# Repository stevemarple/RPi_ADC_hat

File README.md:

# Raspberry Pi ADC hat

A Raspberry Pi hat using the Microchip MCP3424 analogue to digital
converter. The hat also has connectors for I2C and 1-wire interfaces,
and two switched outputs, for instance to control fans, motors or
relays. A Honeywell HIH6130-021 or HIH6131-021 I2C temperature and
humidity sensor can also be fitted.

## Hardware features

### Analogue to digital converter

The MCP3424 is a 4 channel 18 bit differential input analogue to
digital converter. Sample rates are 3.75 SPS (samples per second) at
18 bit resolution, 15 SPS at 16 bit resolution, 60 SPS at 14 bit
resolution and 240 SPS at 12 bit resolution. When single-ended inputs
are used the resolution is reduced by 1 bit. A jumper block enables
the I2C address of the MCP3424 to be selected from eight possible
values. The ADC inputs are directly wired to a 9 pin D connector, 3
channels can be used for differential inputs, the fourth for
single-ended measurements only. Optional decoupling capacitors can be
added to all inputs; alternatively zero ohm resistors may be used to
convert the differential inputs to single-ended.

### I2C interface

The buffered I2C interface is made available via an RJ11 connector,
allowing additional MCP3424 devices or other I2C devices to be
connected, eg the AuroraWatchNet magnetometer sensor head
(https://github.com/stevemarple/AuroraWatchNet/tree/master/hardware/FLC100_shield/remote_v2). 

### 1-wire interface

A connector for a 1-wire interface is provided. The 3 pin Molex
connector also connects to the Raspberry Pi's 3.3V supply so that it
is not necessary to use parasitic power operation.

### Power supplies

All power is used is taken from the Raspberry Pi via the GPIO
header. The 1 wire interface, I2C buffer and HAT EEPROM are connected
to the Pi's 3.3V supply, all other power is derived from the 5V
supply. Changes in the CPU load on the Pi can result in small supply
voltage variations due to voltage sag from the Pi's power supply. When
sensors and the ADC are powered directly from the Pi's 5V supply this
can result in spurious measurements. To combat this effect a DC-DC
converter and linear regulator can be fitted to derive a stable
analogue voltage supply.

### Switched outputs

Two switched outputs are provided which can be connected to fans,
motors, relays etc. Flyback diodes can be fitted to allow safe switching
of inductive loads.

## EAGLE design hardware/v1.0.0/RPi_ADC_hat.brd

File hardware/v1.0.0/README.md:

# Build instructions for v1.0.0

The PCB design offers a number of options for construction, not all
parts should fitted. Indeed, to do so could be harmful to the ADC
HAT and to the Raspberry Pi. Read and understand the build options first.

## Build options

### Linear voltage regulator

Decide upon the analogue supply voltage for your application. The
analogue voltage sets the operating voltage for MCP3424 ADC, and the
signal levels for the buffered section of the I2C bus. There are four
options:

1. For 3.3V operation fit a Microchip TC1262-33VDB. Do not fit the
DC-DC converter, instead fit the DC-DC converter link wire.
2. For a clean 5V analogue supply fit a Microchip MCP1790-5002E/DB
voltage regulator and a DC-DC converter.
3. To reuse the Raspberry Pi's 5V supply (not recommended) do not fit
a voltage regulator and do not fit the DC-DC converter. Fit the link
wires for both the DC-DC converter and the voltage regulator.
4. To delegate the analogue voltage supply generation to an external
board connected via the I2C interface connector X1 do not fit the
voltage regulator or the voltage regulator link wire. Whether the
DC-DC converter should also be fitted depends on the input voltage
required for the external regulator; it can be powered from either the
Pi's 5V supply or the DC-DC converter's output, selected by the
position of the jumper on JP1.

Under no circumstances should the linear regulator and its link wire
be fitted.

Fit JP1 only if option 4 is selected.

### DC-DC converter

The standard DC-DC converter is the  Traco TME0509S. Alternatives
include the Murata NME0509SC and the Recom Power RO-0509S. All
convert 5V DC to 9V DC. Provided the recommended voltage ratings for
the capacitors are followed it is also possible to use 5V to 12V DC-DC
converters.

The reference build is to include a DC-DC converter. If one is not
required then a link wire can be fitted in its place. Under no
circumstances should a DC-DC converter be fitted and its link wire.

It is also possible to use an external supply instead of the DC-DC
converter by fitting a Molex 22-23-2041 connector in its place.

If it is found that the load on the DC-DC converter is insufficient
for correct operation it is possible to fit an optional load resistor
(R3). Do not exceed power rating for the resistor; a 1210
surface-mount resistor can be fitted which is likely to have a higher
rating than the 1206 package.

### ADC

If the onboard ADC is not required (for instance, using external
devices connected to the I2C interface) then omit U4, U6, C6, C11, C12,
C13, C14, C15, C16, C17, X2 and JP2. The reference build is to fit U4,
C6, X2 and JP2.

Decoupling capacitors for the positive inputs of channels 1 (C11), 2
(C12), 3 (C13) and 4 (C14) can be fitted if required. The suggested
value is 100p but the correct value depends on application. Decoupling
capacitors for the negative differential inputs of channels 1 (C15), 2
(C16) and 3 (C17) can also be added. The correct value should probably
match the corresponding decoupling on the positive input but will vary
by application. In the case of single-ended inputs the negative
differential input can be grounded by fitting a zero ohm resistor
instead. Channel 4 is wired as single-ended input only.

### Analogue board temperature

If channel 4 of the onboard ADC is not used then the circuit board
temperature can be monitored by fitting an LM61BIM3 or LM61CIM3
temperature sensor to U6. Also fit C14 (100n).

### Digital humidity and temperature measurement

Relative humidity can be monitored by fitting a Honeywell HIH6130-021
or HIH6131-021 sensor to U3. (Do not confuse these versions with the
similarly-named SPI versions.) Also fit C8 and C9. The sensor also
provides a digital temperature output.

### HAT EEPROM

For compliance with the HAT specifications an EEPROM must be fitted
and programmed accordingly. The recommended part is ON Semiconductor
CAT24C32WI-GT3. Larger capacities, eg ON Semiconductor CAT24C64WI-GT3,
can be fitted instead. In addition to U7 also fit R7, R8, R9, C18 and
JP3. These parts can be omitted if desired but the board cannot be
called a HAT.

Software and instructions for programming the EEPROM can
be found in the Raspberry Pi hats repository, see 
https://github.com/raspberrypi/hats/tree/master/eepromutils.
Predefined device tree configuration files can be found in the
[firmware](../../firmware) directory.

### Switched outputs

Two independent switched 5V outputs can be included to control fans,
motors or relays. For the first switched output fit Q1, R10, R12 C19
and D1 and X4. For the second switched output fit Q2, R11, R13, C20,
D2 and X5. The flyback diodes are essential when inductive loads are
switched.

### External I2C interface

The buffered I2C interface can be made available to external devices
by fitting a 6P6C registered jack to X1. The external buffered side of
the I2C interface operates at the analogue supply voltage.

### 1 wire interface

If the 1 wire interface is desired fit R6 and Molex connector X3. The
interface operates at 3.3V and does not buffer the Raspberry Pi's GPIO
pins - use with caution! RJ11 connectors are frequently used for 1
wire interfaces, do not confuse the RJ11 connector used for the
external I2C interface with the 1 wire interface on the Molex
connector.

## Order of construction

The recommended general order of construction is to solder the top
side components first. Begin with the finest pitch and lowest height
components. Integrated circuits (U3, U4, and U5) should be soldered
first, then the surface mount resistors and capacitors. Then solder
the voltage regulator (U1) and FETs (Q1, Q2). If any components are to
be soldered to the underside turn over and solder those. Then add the
DC-DC converter (U2), the jumper blocks and then the
connectors. Remember that the 40 pin connector is fitted to the
underside (solder from top-side). If any link wires are to be
installed add them last, they provide the ability to test parts of the
circuit separately.

## Bill of materials (BOM)

BOMs for several different build configurations, including the
reference design, can be found in the
[bill_of_materials](bill_of_materials) directory.

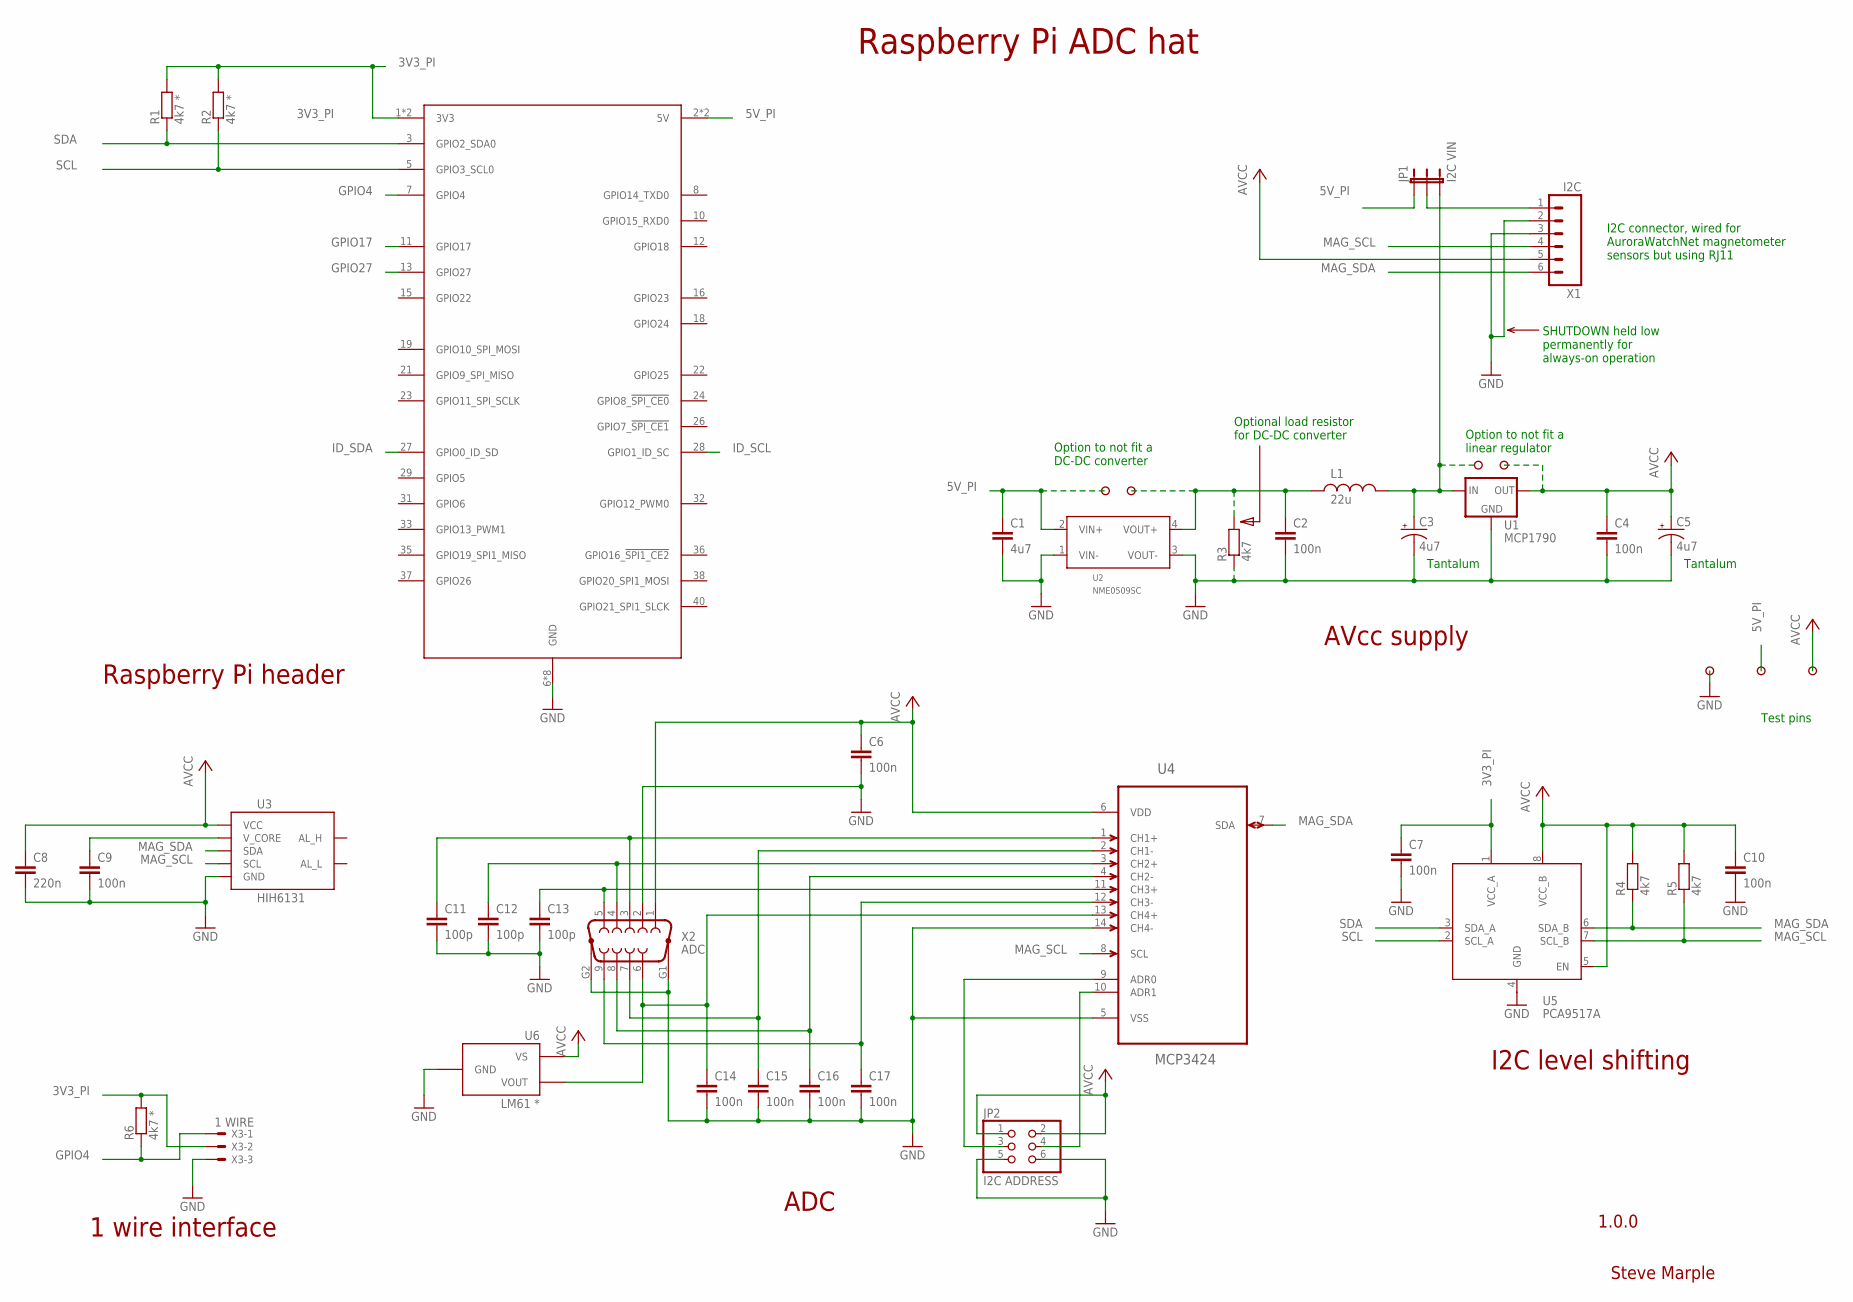
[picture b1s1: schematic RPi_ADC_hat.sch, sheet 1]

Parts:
C1: 4u7; 1206-HAND
C2, C4, C6, C7, C9, C10, C14, C15, C16, C17: 100n; 1206-HAND
C3, C5: 4u7; CPOL-1210-HAND
C8: 220n; 1206-HAND
C11, C12, C13: 100p; 1206-HAND
JP1: I2C VIN; 1X03
JP2: I2C ADDRESS; 2X03
L1: 22u; 1210-HAND
R1, R2, R6: 4k7 *; 1206-HAND
R3: 4k7; 1210-HAND
R4, R5: 4k7; 1206-HAND
U1: MCP1790; SOT223-HAND
U2: NME0509SC; DC-DC-MURATA-NME-05-12-SERIES
U3: HIH6131; SO08
U4: MCP3424; SO14
U5: PCA9517A; SO08
U6: LM61 *; SOT23-3-HAND
U$1: PCB; RASPBERRY-PI-3
U$2, U$3, U$4, U$5, U$6, U$7, U$8: PAD
X1: I2C; RJ11-6
X2: ADC; DSUB-5504F1-02-9PIN
X3: 1 WIRE; 22-23-2031

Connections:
3V3_PI: C7.1, R1.2, R2.2, R6.2, U5.1 (VCC_A), U$1.1 (3V3), U$1.17 (3V3), X3.2; also elsewhere on the board
5V_PI: C1.1, JP1.1, U2.2 (VIN+), U$1.2 (5V), U$1.4 (5V), U$4.1, U$7.1; also elsewhere on the board
AVCC: C4.1, C5.+, C6.1, C8.1, C10.1, JP2.1, JP2.2, R4.2, R5.2, U1.3 (OUT), U3.8 (VCC), U4.6 (VDD), U5.5 (EN), U5.8 (VCC_B), U6.1 (VS), U$3.1, U$8.1, X1.5, X2.1
CH1+: C11.1, U4.1 (CH1+), X2.3
CH1-: C15.1, U4.2 (CH1-), X2.7
CH2+: C12.1, U4.3 (CH2+), X2.4
CH2-: C16.1, U4.4 (CH2-), X2.8
CH3+: C13.1, U4.11 (CH3+), X2.5
CH3-: C17.1, U4.12 (CH3-), X2.9
CH4+: C14.1, U4.13 (CH4+), U6.2 (VOUT), X2.6
DC-DC_OUT: C3.+, JP1.3, L1.2, U1.1 (IN), U$2.1
DC-DC_UNFILTERED: C2.1, L1.1, R3.2, U2.4 (VOUT+), U$5.1
GND: C1.2, C2.2, C3.-, C4.2, C5.-, C6.2, C7.2, C8.2, C9.2, C10.2, C11.2, C12.2, C13.2, C14.2, C15.2, C16.2, C17.2, JP2.5, JP2.6, R3.1, U1.2 (GND), U1.4 (GND), U2.1 (VIN-), U2.3 (VOUT-), U3.2 (GND), U4.5 (VSS), U4.14 (CH4-), U5.4 (GND), U6.3 (GND), U$1.6 (GND), U$1.9 (GND), U$1.14 (GND), U$1.20 (GND), U$1.25 (GND), U$1.30 (GND), U$1.34 (GND), U$1.39 (GND), U$6.1, X1.2, X1.3, X2.2, X2.G1, X2.G2, X3.3; also elsewhere on the board
GPIO4: R6.1, U$1.7 (GPIO4), X3.1
GPIO17: U$1.11 (GPIO17); also elsewhere on the board
GPIO27: U$1.13 (GPIO27); also elsewhere on the board
HIH_VCORE: C9.1, U3.1 (V_CORE)
I2C_VIN: JP1.2, X1.1
ID_SCL: U$1.28 (GPIO1_ID_SC); also elsewhere on the board
ID_SDA: U$1.27 (GPIO0_ID_SD); also elsewhere on the board
MAG_SCL: R5.1, U3.3 (SCL), U4.8 (SCL), U5.7 (SCL_B), X1.4
MAG_SDA: R4.1, U3.4 (SDA), U4.7 (SDA), U5.6 (SDA_B), X1.6
unnamed: JP2.3, U4.9 (ADR0)
unnamed: JP2.4, U4.10 (ADR1)
SCL: R2.1, U5.2 (SCL_A), U$1.5 (GPIO3_SCL0)
SDA: R1.1, U5.3 (SDA_A), U$1.3 (GPIO2_SDA0)

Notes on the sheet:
Steve Marple
1.0.0
SHUTDOWN held low permanently for always-on operation
Raspberry Pi ADC hat
AVcc supply
Option to not fit a DC-DC converter
Tantalum
Optional load resistor for DC-DC converter
1 wire interface
I2C level shifting
ADC
Raspberry Pi header
Test pins
Option to not fit a linear regulator
I2C connector, wired for AuroraWatchNet magnetometer sensors but using RJ11

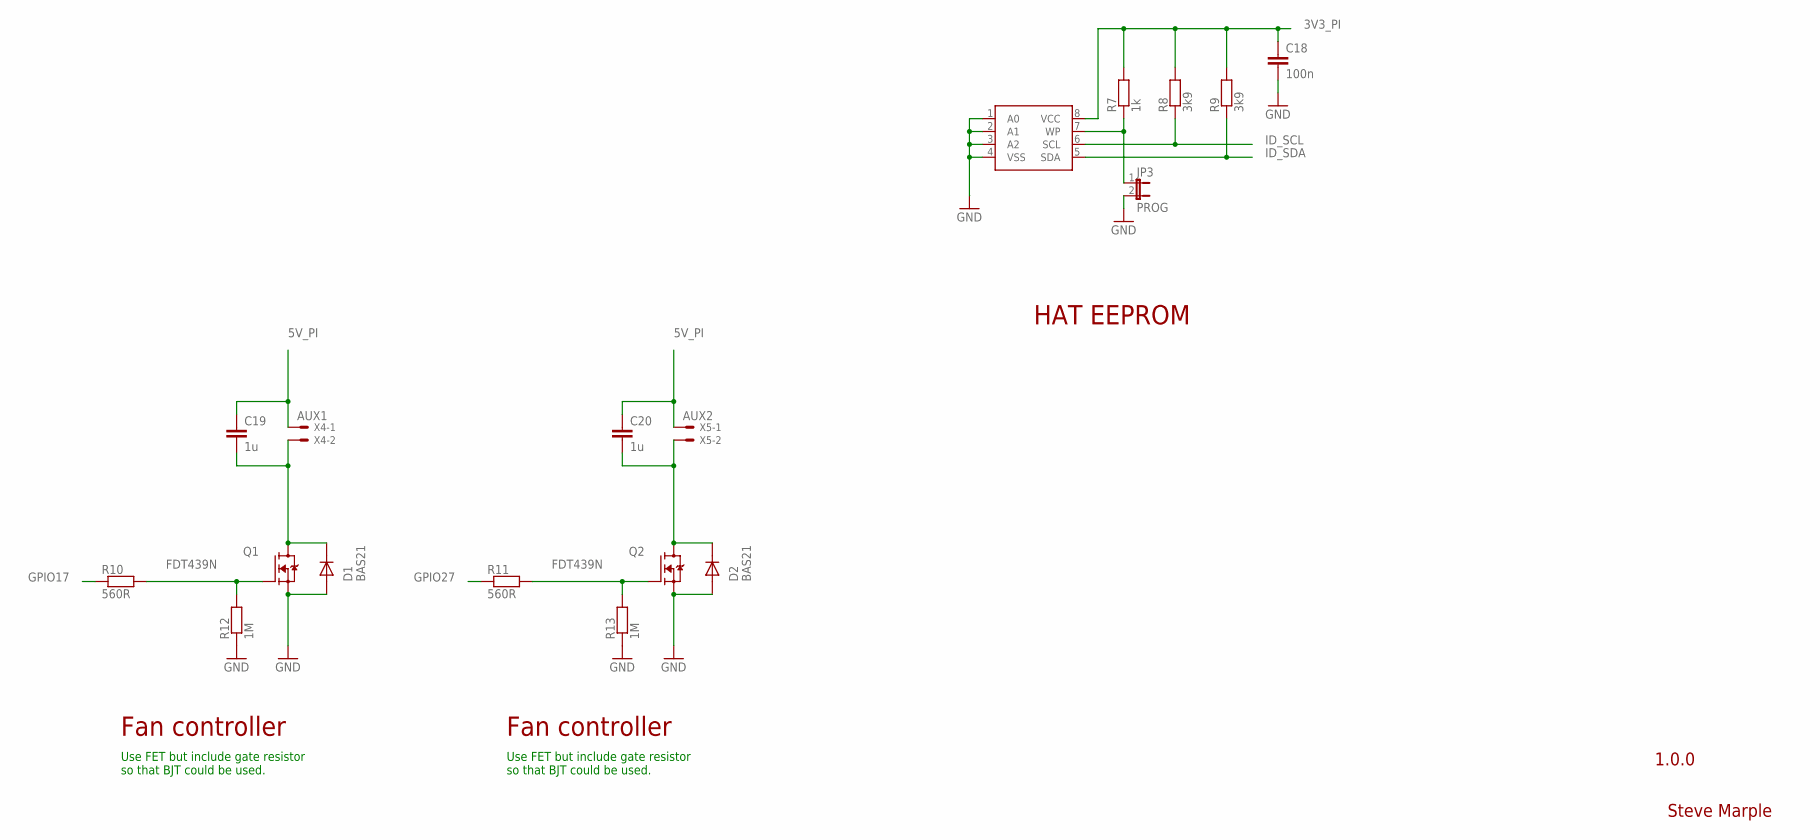
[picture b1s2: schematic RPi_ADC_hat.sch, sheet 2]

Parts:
C18: 100n; 1206-HAND
C19, C20: 1u; 1206-HAND
D1, D2: BAS21; SOT23-3-HAND
JP3: PROG; 1X02
Q1, Q2: FDT439N; SOT223-HAND
R7: 1k; 1206-HAND
R8, R9: 3k9; 1206-HAND
R10, R11: 560R; 1206-HAND
R12, R13: 1M; 1206-HAND
U7: C24C32; SO08
X4: AUX1; 22-23-2021
X5: AUX2; 22-23-2021

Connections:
3V3_PI: C18.1, R7.2, R8.2, R9.2, U7.8 (VCC); also elsewhere on the board
5V_PI: C19.1, C20.1, X4.1, X5.1; also elsewhere on the board
EEPROM_WP: JP3.1, R7.1, U7.7 (WP)
FAN1_CTRL: C19.2, D1.3 (C), Q1.2 (D), Q1.4 (D), X4.2
FAN2_CTRL: C20.2, D2.3 (C), Q2.2 (D), Q2.4 (D), X5.2
GND: C18.2, D1.1 (A), D2.1 (A), JP3.2, Q1.3 (S), Q2.3 (S), R12.1, R13.1, U7.1 (A0), U7.2 (A1), U7.3 (A2), U7.4 (VSS); also elsewhere on the board
GPIO17: R10.1; also elsewhere on the board
GPIO27: R11.1; also elsewhere on the board
ID_SCL: R8.1, U7.6 (SCL); also elsewhere on the board
ID_SDA: R9.1, U7.5 (SDA); also elsewhere on the board
unnamed: Q2.1 (G), R11.2, R13.2
unnamed: Q1.1 (G), R10.2, R12.2

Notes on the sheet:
Fan controller
Use FET but include gate resistor so that BJT could be used.
Steve Marple
1.0.0
HAT EEPROM

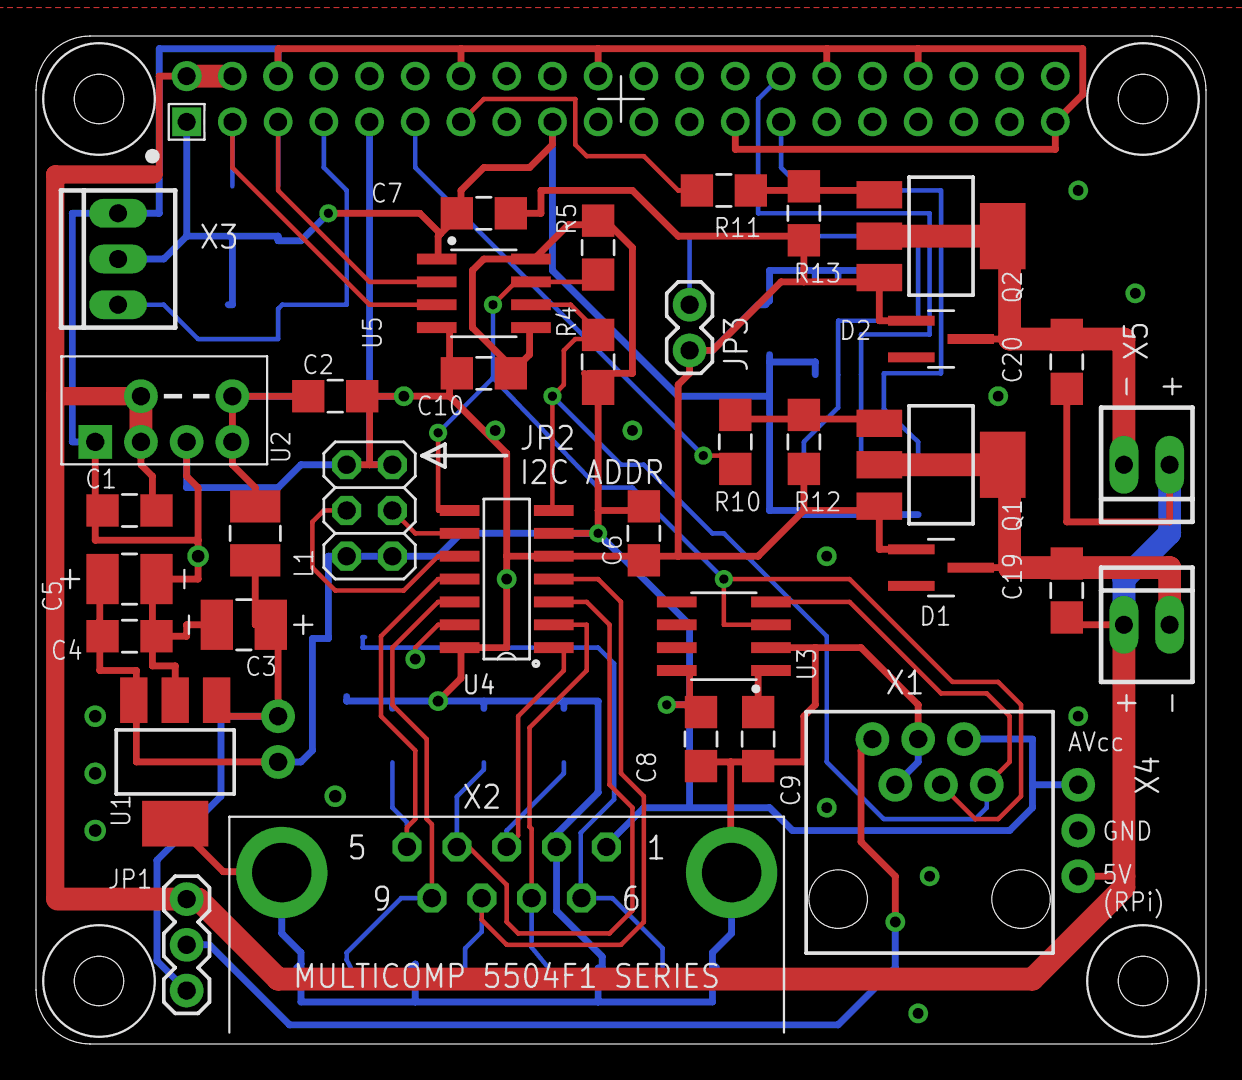
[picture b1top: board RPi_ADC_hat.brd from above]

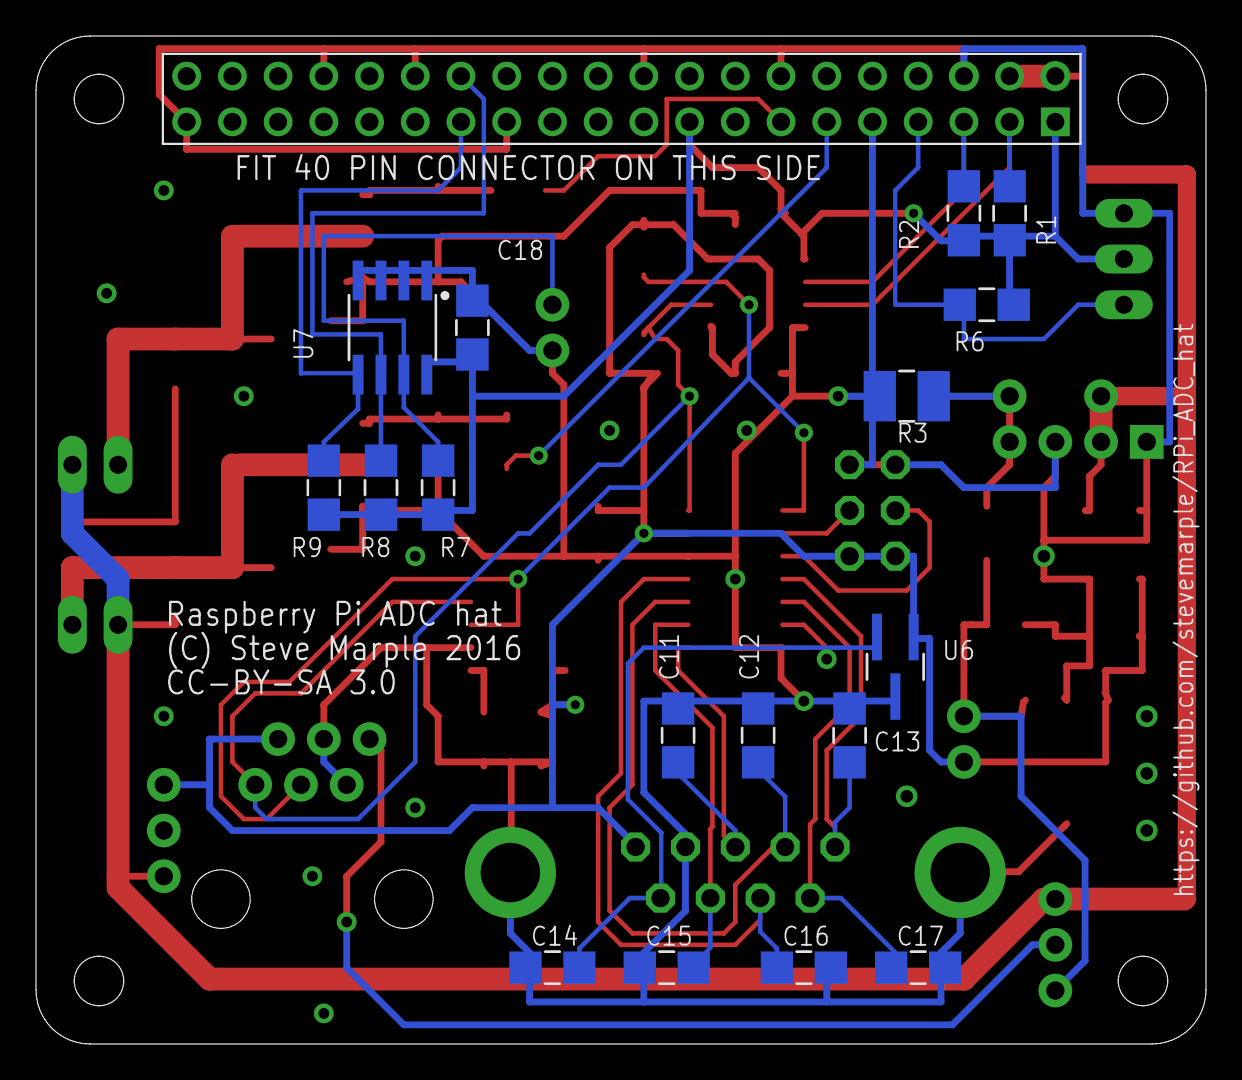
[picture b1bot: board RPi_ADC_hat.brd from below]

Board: 2 copper layers, 65.0 x 56.0 mm, 61 parts (17 on the bottom side), 31 nets.

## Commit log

2016-09-11 Increase gate resistors, renumber parts
    Resistors on FET gate increased to more closely match the value
    that would be needed if the FET is replaced by a BJT.
2016-09-11 Update hardware information
2016-09-11 Minor fixes to silkscreen
2016-09-11 Add design rules files
2016-09-11 Add CAM file
2016-09-11 Add Gerber files
2016-09-11 Minor fix to text width
    Widtch of "LM61" increased from 8% to 10%.
2016-09-12 Describe all build options and add build instructions
2016-09-12 Rename build instructions so it shows more clearly on Github
2016-09-13 Correct typos
2016-09-13 Add information about optional load resistor for DC-DC converter
2016-09-13 Add (partial) BOM for the reference design
2016-09-18 Inital EEPROM settings for reference build
    I2C, 1-wire interfaces and both auxiliary switches included.
2016-09-24 Add column indicating which parts to be fitted
    Also add more manufacturer part numbers and order codes.
2016-09-24 Add manufacturer part number and order code for R7
2016-09-24 Add BOM for AuroraWatchNet Raspberry Pi magnetometer
2016-09-24 Update build information
2016-09-24 Fix link
2016-09-25 Fix build instructions
2016-09-29 Fix name
2016-09-29 Add firmware for AWN Raspberry Pi magnetometer build
2016-09-29 Remove firmware
    Image contains GUID, create as needed locally.
2016-09-29 Ignore EEPROM images
2016-09-30 Remove parts from BOM which are not fitted
2016-11-08 Add decoupling for output when LM61 fitted
2016-11-09 Add device tree config for AuroraWatch UK camera controller
2017-06-27 Fix typo
2017-06-27 Add BOM for camera controller
2017-06-27 Add humidity sensor part number and order codes
2017-06-28 Add inductor
2017-07-03 Add extra components
    C11, C12, C13: decoupling capacitors.
    C15, C16, C17: 0 ohm resistors to convert double-ended input to single-
    ended input by grounding -ve input.
2017-07-03 Add reference to EEPROM tools
2017-07-03 Link to predefined device tree config files
2017-07-05 Update information about flyback diodes
2017-10-16 Add schematic and PCB layout as PDFs

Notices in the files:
hardware/v1.0.0/RPi_ADC_hat.brd:
CC-BY-SA 3.0
